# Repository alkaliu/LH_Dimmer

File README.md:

# LH_Dimmer
Led strip dimmer based on Arduino(ProMicro), PCA9685, and mosfets

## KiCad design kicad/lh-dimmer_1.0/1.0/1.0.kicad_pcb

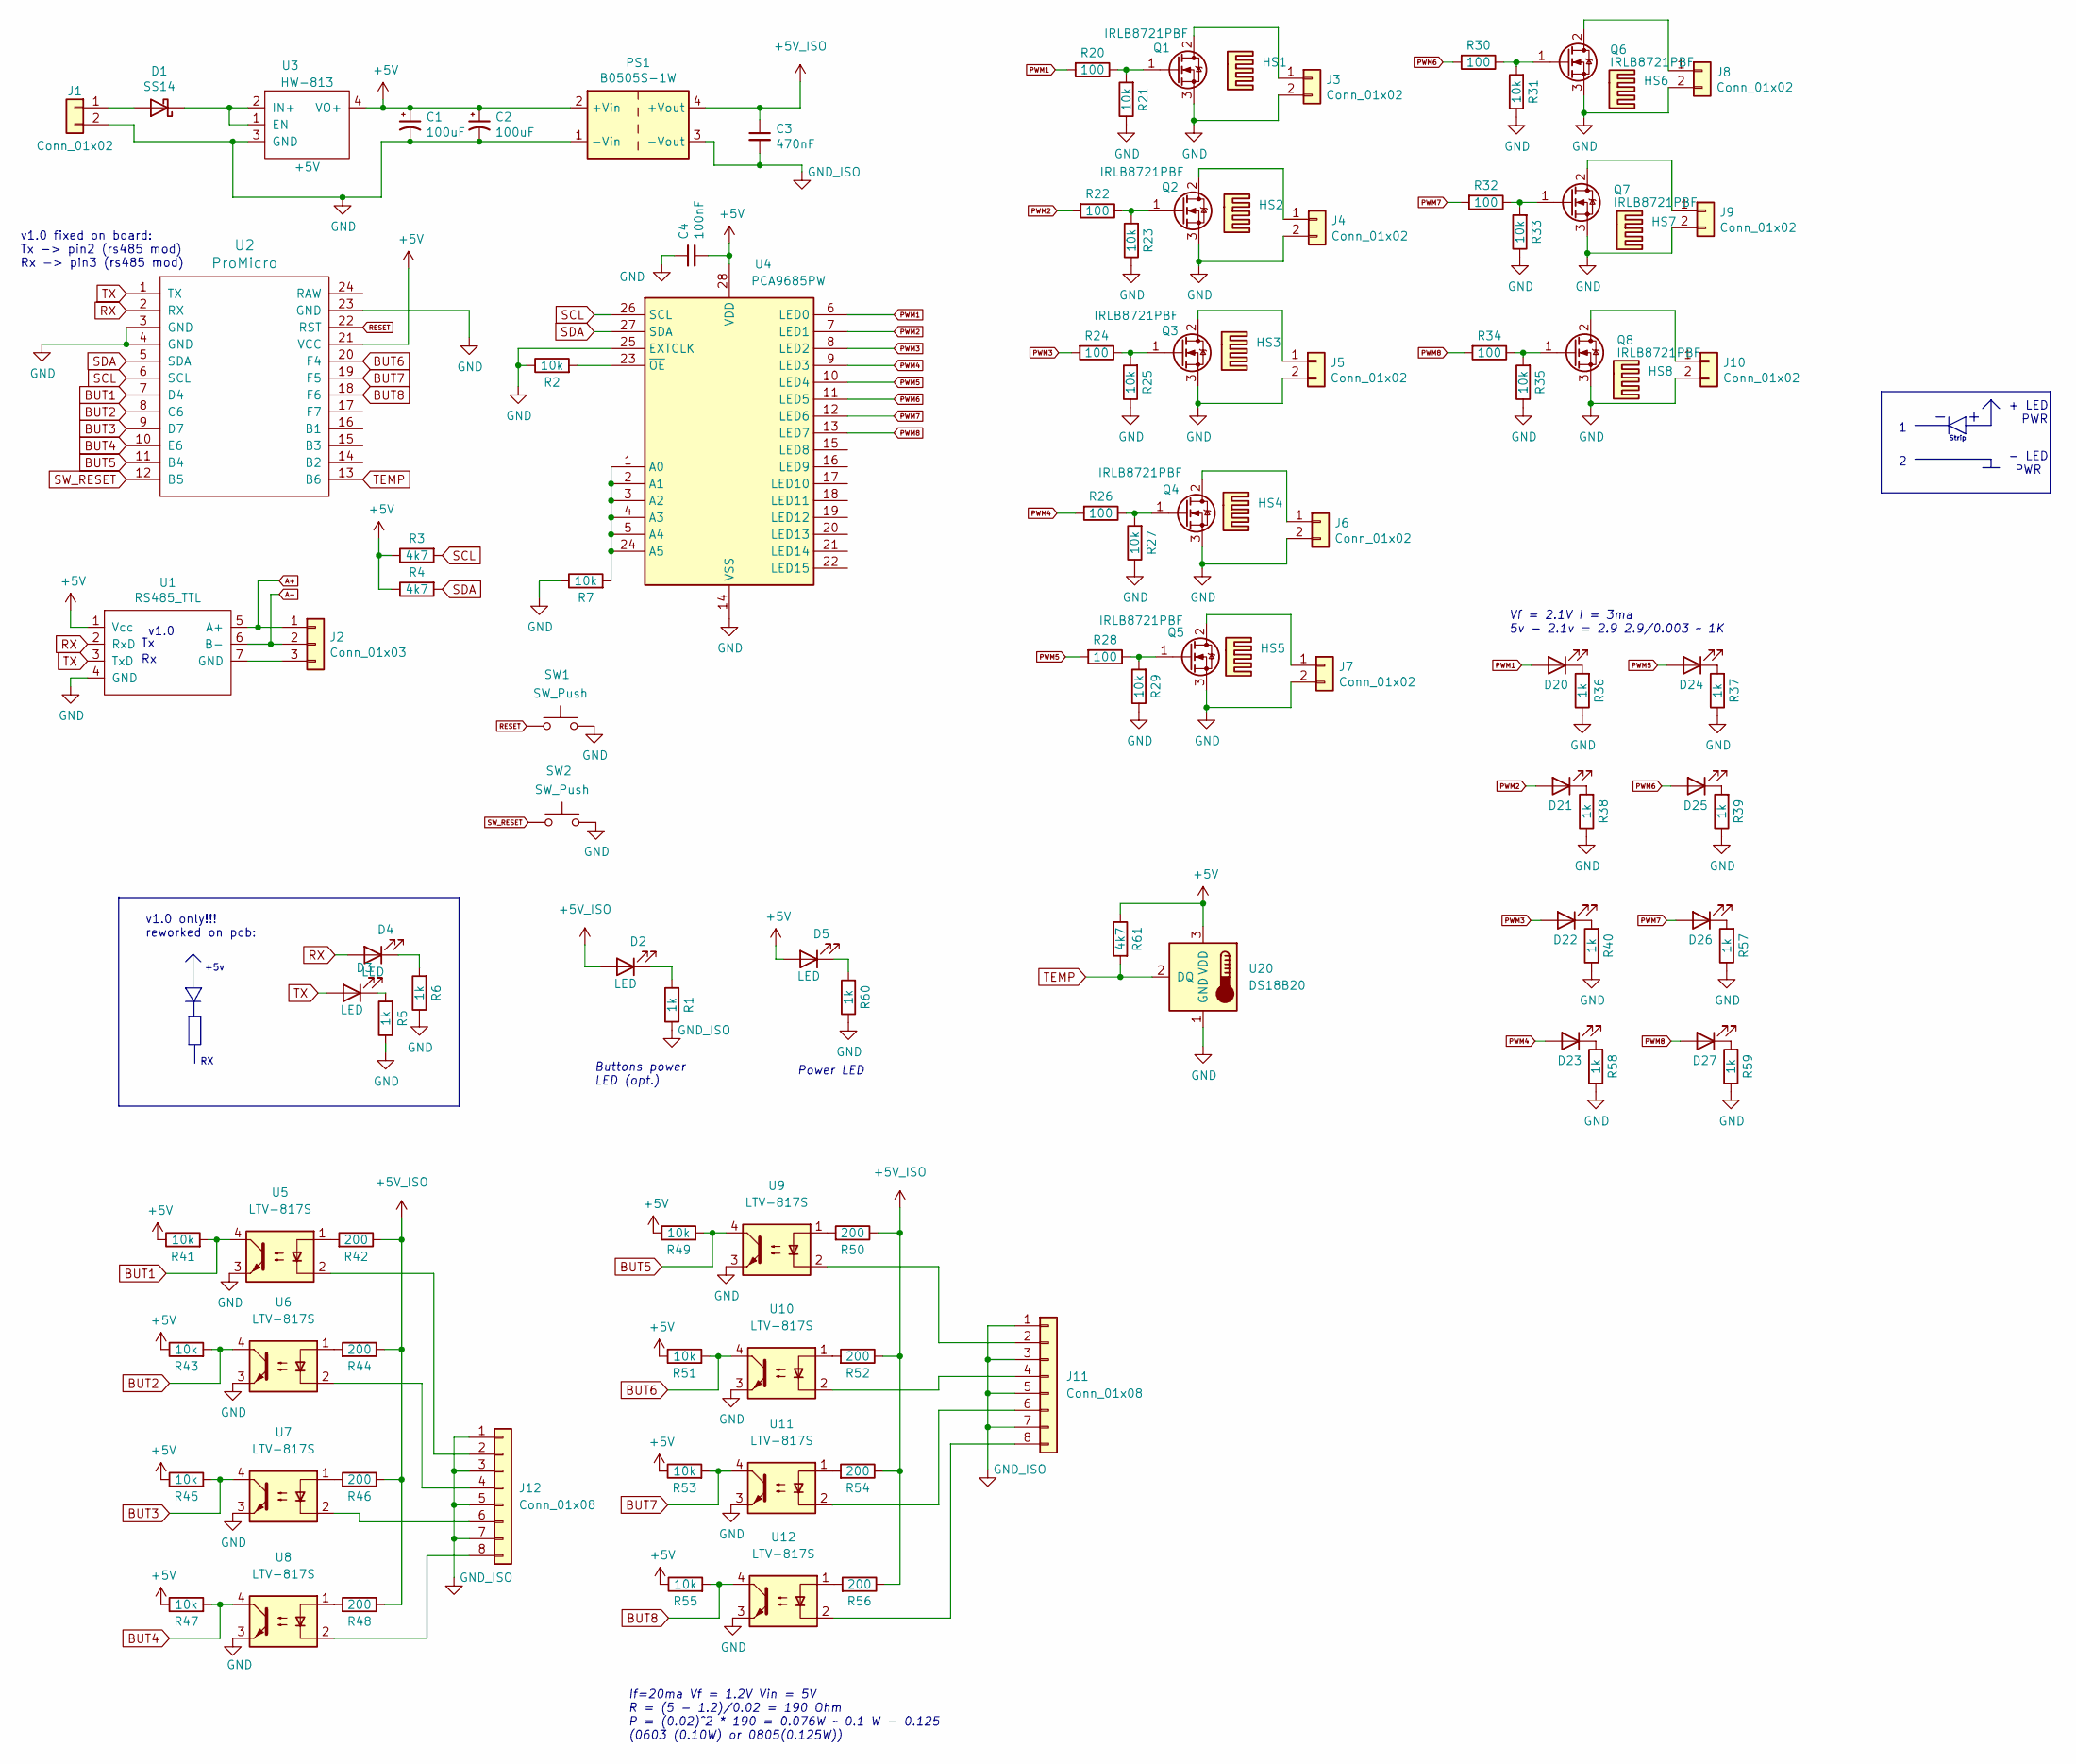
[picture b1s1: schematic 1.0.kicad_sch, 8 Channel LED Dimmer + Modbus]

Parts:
C1, C2: 100uF; CP_Radial_D8.0mm_P3.50mm
C3: 470nF; C_1206_3216Metric_Pad1.33x1.80mm_HandSolder
C4: 100nF; C_1206_3216Metric_Pad1.33x1.80mm_HandSolder
D1: SS14; D_SMA
D2, D3, D4, D5, D20, D21, D22, D23, D24, D25, D26, D27: LED; LED_D3.0mm
HS1, HS2, HS3, HS4, HS5, HS6, HS7, HS8: Heatsink; DY-CN-025
J1, J3, J4, J5, J6, J7, J8, J9, J10: Conn_01x02; PhoenixContact_MSTBA_2,5_2-G-5,08_1x02_P5.08mm_Horizontal
J2: Conn_01x03; PhoenixContact_MSTBA_2,5_3-G-5,08_1x03_P5.08mm_Horizontal
J11, J12: Conn_01x08; PhoenixContact_MSTBA_2,5_8-G-5,08_1x08_P5.08mm_Horizontal
PS1: B0505S-1W; Converter_DCDC_Murata_MEE1SxxxxSC_THT
Q1, Q2, Q3, Q4, Q5, Q6, Q7, Q8: IRLB8721PBF; TO-220-3_Vertical
R1, R5, R6, R36, R37, R38, R39, R40, R57, R58, R59, R60: 1k; R_0805_2012Metric_Pad1.20x1.40mm_HandSolder
R2, R7, R21, R23, R25, R27, R29, R31, R33, R35, R41, R43, R45, R47, R49, R51, R53, R55: 10k; R_0805_2012Metric_Pad1.20x1.40mm_HandSolder
R3, R4, R61: 4k7; R_0805_2012Metric_Pad1.20x1.40mm_HandSolder
R20, R22, R24, R26, R28, R30, R32, R34: 100; R_0805_2012Metric_Pad1.20x1.40mm_HandSolder
R42, R44, R46, R48, R50, R52, R54, R56: 200; R_0805_2012Metric_Pad1.20x1.40mm_HandSolder
SW1, SW2: SW_Push; SW_PUSH_6mm_H4.3mm
U1: RS485_TTL; RS485_TTL_1
U2: ProMicro; ProMicroDsh
U3: HW-813; HM813_V_A
U4: PCA9685PW; TSSOP-28_4.4x9.7mm_P0.65mm
U5, U6, U7, U8, U9, U10, U11, U12: LTV-817S; SMDIP-4_W9.53mm
U20: DS18B20; TO-92_Inline

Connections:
+5V: C1.1, C2.1, C4.2, D5.2 (A), PS1.2 (+Vin), R3.1, R4.1, R41.1, R43.1, R45.1, R47.1, R49.1, R51.1, R53.1, R55.1, R61.1, U1.1 (Vcc), U2.21 (VCC), U3.4 (VO+), U4.28 (VDD), U20.3 (VDD)
+5V_ISO: C3.1, D2.2 (A), PS1.4 (+Vout), R42.1, R44.1, R46.1, R48.1, R50.1, R52.1, R54.1, R56.1
A+: J2.1, U1.5 (A+)
A-: J2.2, U1.6 (B-)
BUT1: R41.2, U2.7 (D4), U5.4
BUT2: R43.2, U2.8 (C6), U6.4
BUT3: R45.2, U2.9 (D7), U7.4
BUT4: R47.2, U2.10 (E6), U8.4
BUT5: R49.2, U2.11 (B4), U9.4
BUT6: R51.2, U2.20 (F4), U10.4
BUT7: R53.2, U2.19 (F5), U11.4
BUT8: R55.2, U2.18 (F6), U12.4
GND: C1.2, C2.2, C4.1, J1.2, J3.2, J4.2, J5.2, J6.2, J7.2, J8.2, J9.2, J10.2, PS1.1 (-Vin), Q1.3 (S), Q2.3 (S), Q3.3 (S), Q4.3 (S), Q5.3 (S), Q6.3 (S), Q7.3 (S), Q8.3 (S), R2.1, R5.1, R6.1, R7.1, R21.1, R23.1, R25.1, R27.1, R29.1, R31.1, R33.1, R35.1, R36.1, R37.1, R38.1, R39.1, R40.1, R57.1, R58.1, R59.1, R60.1, SW1.2, SW2.2, U1.4 (GND), U2.3 (GND), U2.4 (GND), U2.23 (GND), U3.3 (GND), U4.14 (VSS), U4.25 (EXTCLK), U5.3, U6.3, U7.3, U8.3, U9.3, U10.3, U11.3, U12.3, U20.1 (GND)
GND_ISO: C3.2, J11.1, J11.3, J11.5, J11.7, J12.1, J12.3, J12.5, J12.7, PS1.3 (-Vout), R1.1
unnamed: D1.1 (K), U3.1 (EN), U3.2 (IN+)
unnamed: D1.2 (A), J1.1
unnamed: D2.1 (K), R1.2
unnamed: D3.1 (K), R5.2
unnamed: D4.1 (K), R6.2
unnamed: D5.1 (K), R60.2
unnamed: J2.3, U1.7 (GND)
unnamed: J3.1, Q1.2 (D)
unnamed: J4.1, Q2.2 (D)
unnamed: J5.1, Q3.2 (D)
unnamed: J6.1, Q4.2 (D)
unnamed: J7.1, Q5.2 (D)
unnamed: J8.1, Q6.2 (D)
unnamed: J9.1, Q7.2 (D)
unnamed: J10.1, Q8.2 (D)
unnamed: J11.2, U9.2
unnamed: J11.4, U10.2
unnamed: J11.6, U11.2
unnamed: J11.8, U12.2
unnamed: J12.2, U5.2
unnamed: J12.4, U6.2
unnamed: J12.6, U7.2
unnamed: J12.8, U8.2
unnamed: Q1.1 (G), R20.1, R21.2
unnamed: Q2.1 (G), R22.1, R23.2
unnamed: Q3.1 (G), R24.1, R25.2
unnamed: Q4.1 (G), R26.1, R27.2
unnamed: Q5.1 (G), R28.1, R29.2
unnamed: Q6.1 (G), R30.1, R31.2
unnamed: Q7.1 (G), R32.1, R33.2
unnamed: Q8.1 (G), R34.1, R35.2
unnamed: R2.2, U4.23 (~OE)
unnamed: R7.2, U4.1 (A0), U4.2 (A1), U4.3 (A2), U4.4 (A3), U4.5 (A4), U4.24 (A5)
unnamed: D20.1 (K), R36.2
unnamed: D24.1 (K), R37.2
unnamed: D21.1 (K), R38.2
unnamed: D25.1 (K), R39.2
unnamed: D22.1 (K), R40.2
unnamed: R42.2, U5.1
unnamed: R44.2, U6.1
unnamed: R46.2, U7.1
unnamed: R48.2, U8.1
unnamed: R50.2, U9.1
unnamed: R52.2, U10.1
unnamed: R54.2, U11.1
unnamed: R56.2, U12.1
unnamed: D26.1 (K), R57.2
unnamed: D23.1 (K), R58.2
unnamed: D27.1 (K), R59.2
PWM1: D20.2 (A), R20.2, U4.6 (LED0)
PWM2: D21.2 (A), R22.2, U4.7 (LED1)
PWM3: D22.2 (A), R24.2, U4.8 (LED2)
PWM4: D23.2 (A), R26.2, U4.9 (LED3)
PWM5: D24.2 (A), R28.2, U4.10 (LED4)
PWM6: D25.2 (A), R30.2, U4.11 (LED5)
PWM7: D26.2 (A), R32.2, U4.12 (LED6)
PWM8: D27.2 (A), R34.2, U4.13 (LED7)
RESET: SW1.1, U2.22 (RST)
RX: D4.2 (A), U1.2 (RxD), U2.2 (RX)
SCL: R3.2, U2.6 (SCL), U4.26 (SCL)
SDA: R4.2, U2.5 (SDA), U4.27 (SDA)
SW_RESET: SW2.1, U2.12 (B5)
TEMP: R61.2, U2.13 (B6), U20.2 (DQ)
TX: D3.2 (A), U1.3 (TxD), U2.1 (TX)

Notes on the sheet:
Buttons power LED (opt.)
v1.0
Strip
- LED PWR
v1.0 fixed on board: Tx -> pin2 (rs485 mod) Rx -> pin3 (rs485 mod)
Power LED
+5v
v1.0 only!!! reworked on pcb:
Vf = 2.1V I = 3ma 5v - 2.1v = 2.9 2.9/0.003 ~ 1K
If=20ma Vf = 1.2V Vin = 5V R = (5 - 1.2)/0.02 = 190 Ohm P = (0.02)^2 * 190 = 0.076W ~ 0.1 W - 0.125 (0603 (0.10W) or 0805(0.125W))
+ LED PWR

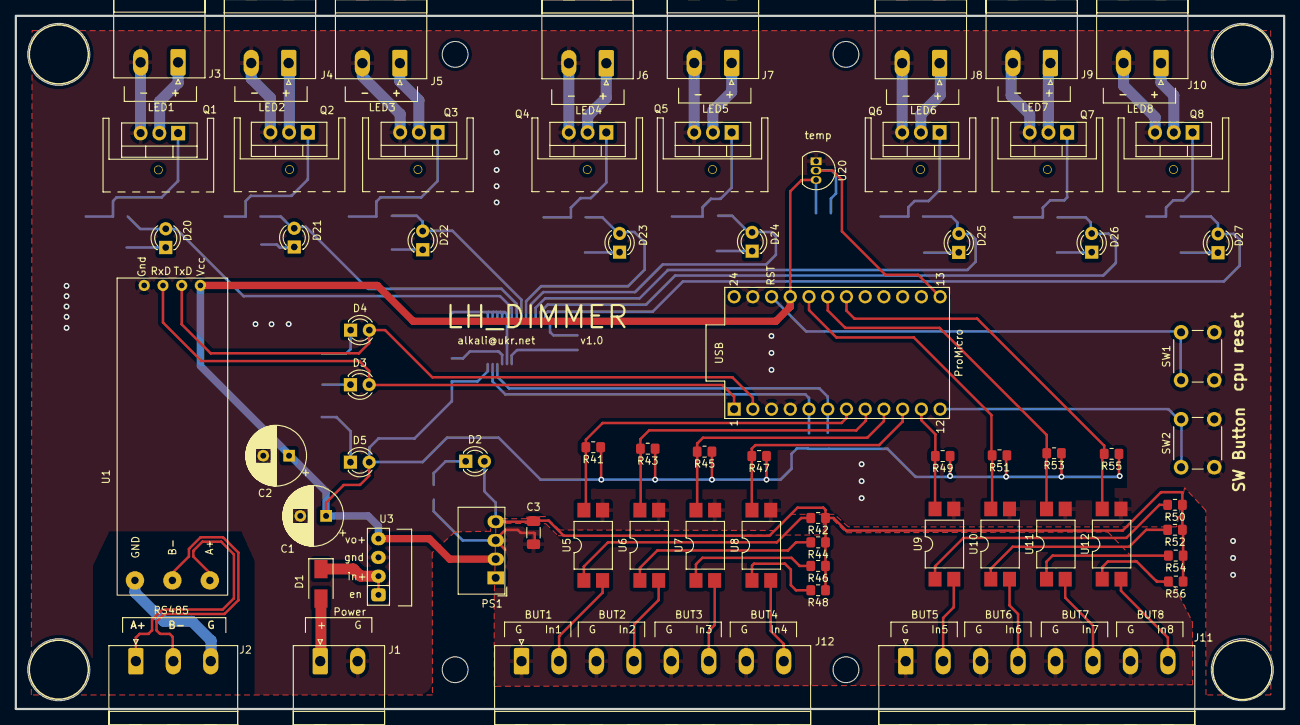
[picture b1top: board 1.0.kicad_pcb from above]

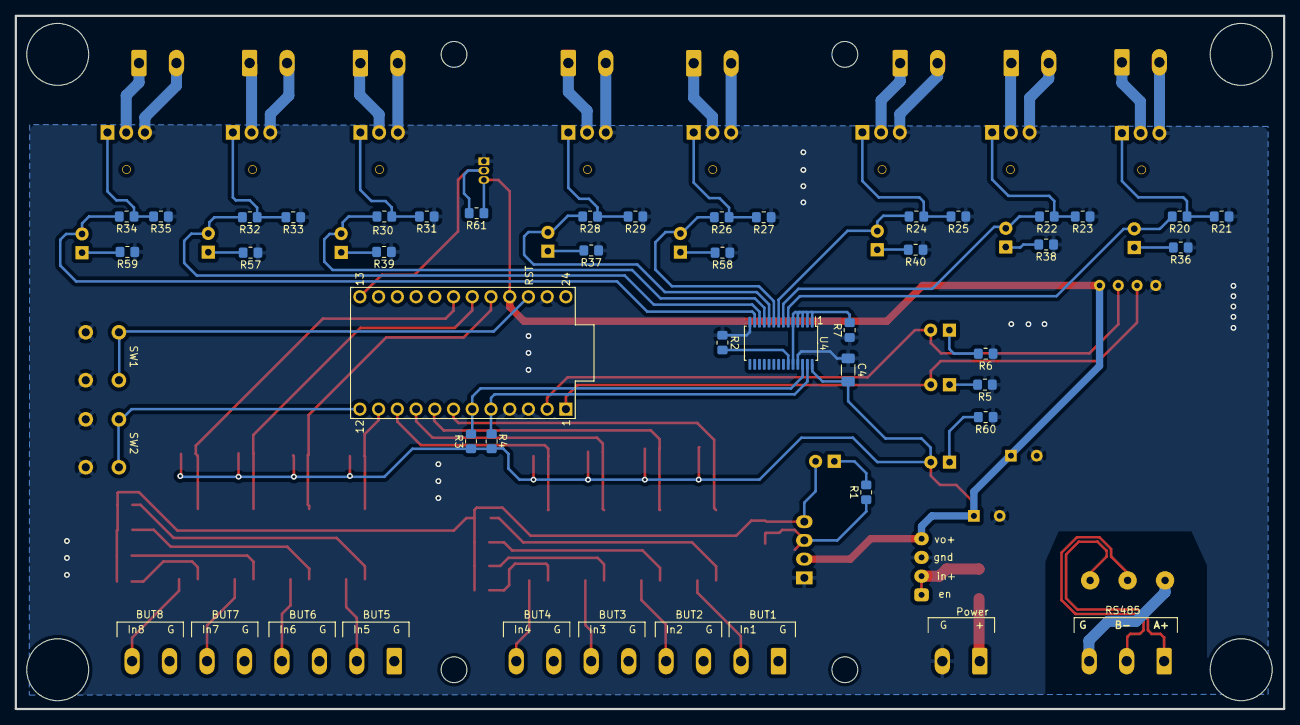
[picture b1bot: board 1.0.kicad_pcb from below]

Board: 2 copper layers, 172.0 x 94.0 mm, 110 parts (35 on the bottom side), 78 nets.

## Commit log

2022-10-06 Load version 1.0 code+sch+pcb
2022-10-06 Add modbus registers map
